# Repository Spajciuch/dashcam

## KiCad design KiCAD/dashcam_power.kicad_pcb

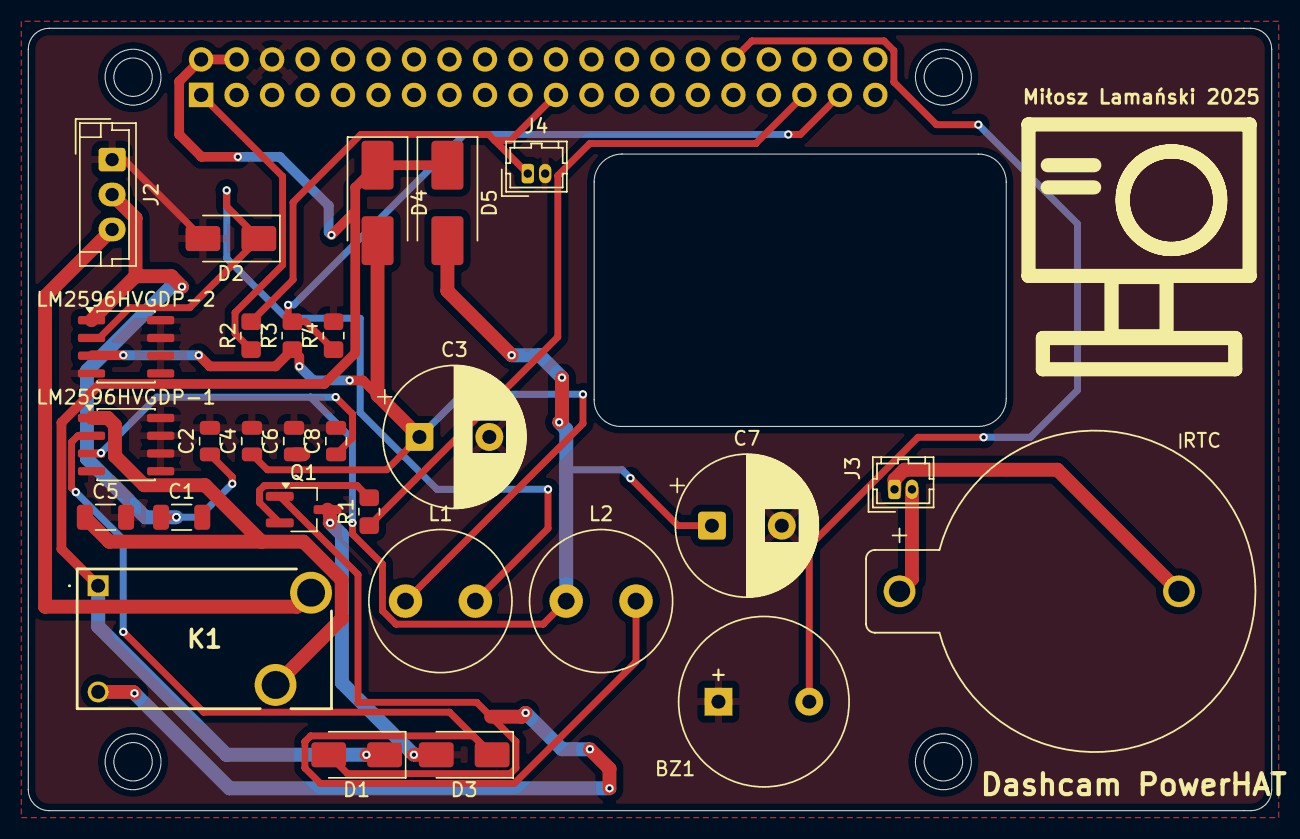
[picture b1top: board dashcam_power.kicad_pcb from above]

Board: 2 copper layers, 89.0 x 56.0 mm, 29 parts (0 on the bottom side), 18 nets.

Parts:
BZ1: Buzzer; MagneticBuzzer_StarMicronics_QMX
C1, C5: 100µF; C_1206_3216Metric
C2, C4, C6, C8: 0.1µF; C_0805_2012Metric
C3, C7: 1000µF; CP_Radial_D10.0mm_P5.00mm
D1: D; D_SMA
D2, D3: D_Schottky; D_SMA
D4, D5: D; D_SMB_Handsoldering
J2: Conn_01x03_Pin; JST_EH_B3B-EH-A_1x03_P2.50mm_Vertical
J3: RTC_OUT; Hirose_DF13-02P-1.25DSA_1x02_P1.25mm_Vertical
J4: RESET_BTN; Hirose_DF13-02P-1.25DSA_1x02_P1.25mm_Vertical
J5: Conn_02x20_Odd_Even; orangepi_3b
K1: AHQSH105LM100G
L1, L2: L; L_Radial_D10.0mm_P5.00mm_Neosid_SD12k_style3
LM2596HVGDP-1, LM2596HVGDP-2: SOIC-8_3.9x4.9mm_P1.27mm
Q1: NPN; TSOT-23_HandSoldering
R1: 1K; R_0805_2012Metric_Pad1.20x1.40mm_HandSolder
R2: 10K; R_0805_2012Metric_Pad1.20x1.40mm_HandSolder
R3: 1K07; R_0805_2012Metric_Pad1.20x1.40mm_HandSolder
R4: 1K96; R_0805_2012Metric_Pad1.20x1.40mm_HandSolder
RTC: 1066; BAT_1066

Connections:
/3.3V: J5.1, R2.1
/5V: D1.1 (K), D4.1 (K), D5.1 (K), J5.2, J5.4, K1.1 (COIL_1)
/5V_ACC: C3.1, C4.1, D4.2 (A), L1.1, LM2596HVGDP-2.3 (FB/ADJ), R3.1
/5V_BATT: C7.1, C8.1, D5.2 (A), L2.1, LM2596HVGDP-1.3 (FB/ADJ)
/12_ACC: C1.1, C2.1, J2.2, LM2596HVGDP-2.1 (VIN)
/12_BATT_IN: J2.3, K1.4 (NO)
/12_BATT_OUT: C5.1, C6.1, K1.3 (COM), LM2596HVGDP-1.1 (VIN)
/ACC_SENSE: J5.37, R3.2, R4.1
/BUZZ: BZ1.2 (-), J5.32
/RELAY_ENABLE: J5.35, R1.1
/RESET_BTN: J4.1, J5.21, R2.2
GND: BZ1.1 (+), C1.2, C2.2, C3.2, C4.2, C5.2, C6.2, C7.2, C8.2, D2.2 (A), D3.2 (A), J2.1, J4.2, J5.6, LM2596HVGDP-1.4 (ON/OFF), LM2596HVGDP-1.5 (GNG), LM2596HVGDP-1.6 (GND), LM2596HVGDP-1.7 (GND), LM2596HVGDP-1.8 (GND), LM2596HVGDP-2.4 (ON/OFF), LM2596HVGDP-2.5 (GNG), LM2596HVGDP-2.6 (GND), LM2596HVGDP-2.7 (GND), LM2596HVGDP-2.8 (GND), Q1.3 (E), R4.2
unnamed: D1.2 (A), K1.2 (COIL_2), Q1.1 (C)
unnamed: D2.1 (K), L1.2, LM2596HVGDP-2.2 (VOUT)
unnamed: D3.1 (K), L2.2, LM2596HVGDP-1.2 (VOUT)
unnamed: J3.1, RTC.N
unnamed: J3.2, RTC.P
unnamed: Q1.2 (B), R1.2

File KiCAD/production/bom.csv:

Designator,Footprint,Quantity,Value,LCSC Part #
BZ1,MagneticBuzzer_StarMicronics_QMX,1,Buzzer,
"C1, C5",1206,2,100µF,
"C2, C4, C6, C8",0805,4,0.1µF,
"C3, C7",CP_Radial_D10.0mm_P5.00mm,2,1000µF,
D1,D_SMA,1,D,
"D2, D3",D_SMA,2,D_Schottky,
"D4, D5",D_SMB_Handsoldering,2,D,
J2,JST_EH_B3B-EH-A_1x03_P2.50mm_Vertical,1,Conn_01x03_Pin,
J3,Hirose_DF13-02P-1.25DSA_1x02_P1.25mm_Vertical,1,RTC_OUT,
J4,Hirose_DF13-02P-1.25DSA_1x02_P1.25mm_Vertical,1,RESET_BTN,
J5,orangepi_3b,1,Conn_02x20_Odd_Even,
K1,AHQSH105LM100G,1,AHQSH105LM100G,
"L1, L2",L_Radial_D10.0mm_P5.00mm_Neosid_SD12k_style3,2,L,
"LM2596HVGDP-1, LM2596HVGDP-2",SOIC-8_3.9x4.9mm_P1.27mm,2,~,
Q1,TSOT-23_HandSoldering,1,NPN,
R1,0805,1,1K,
R2,0805,1,10K,
R3,0805,1,1K07,
R4,0805,1,1K96,
RTC,BAT_1066,1,1066,
